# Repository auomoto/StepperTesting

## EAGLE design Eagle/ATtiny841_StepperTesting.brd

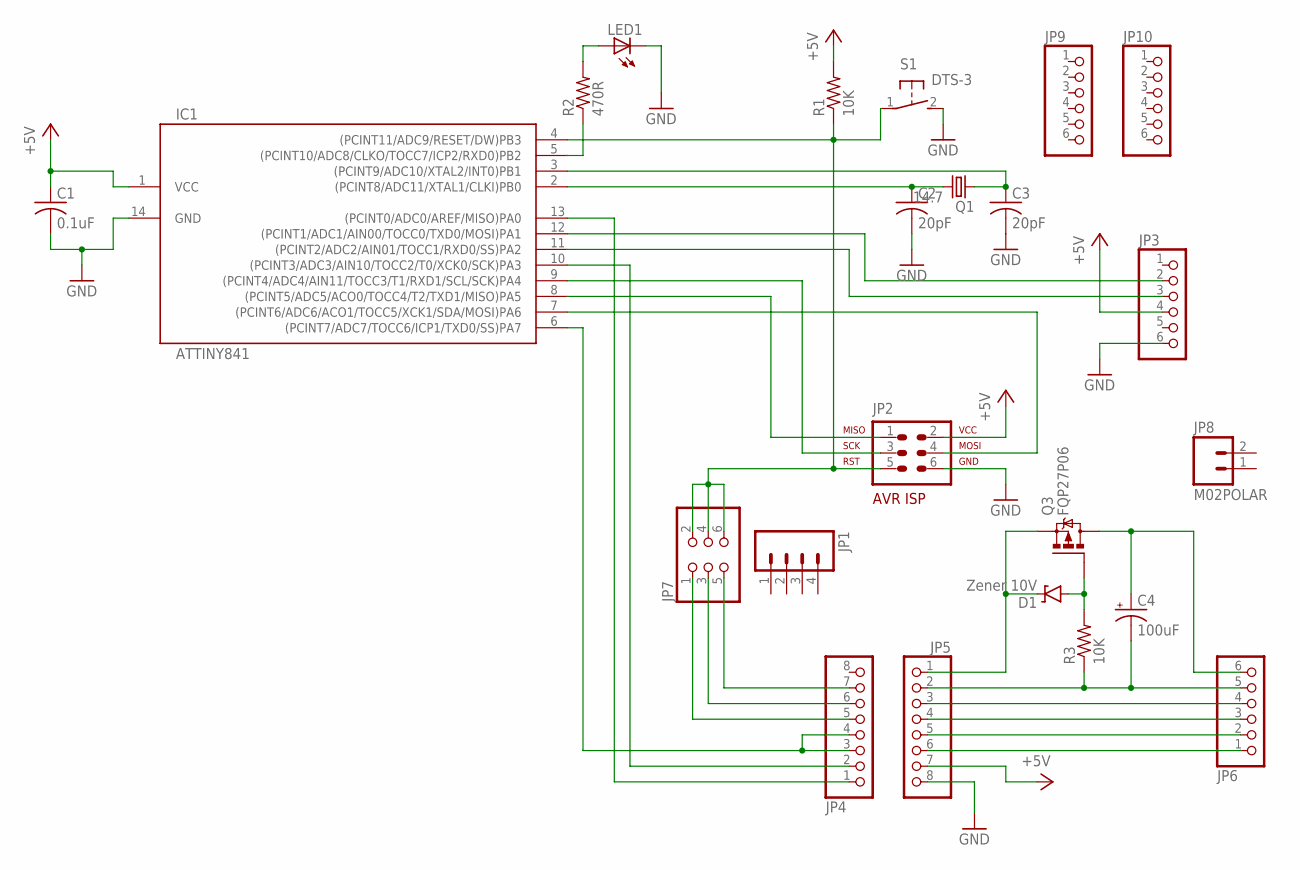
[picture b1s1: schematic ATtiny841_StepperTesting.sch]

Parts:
C1: 0.1uF; C025-024X044
C2, C3: 20pF; C025-024X044
C4: 100uF; E3,5-8
D1: Zener 10V; DIODE-ZENER
IC1: ATTINY841; SOIC14
JP1: M04POLAR; MOLEX-1X4
JP2: AVR-ISP-6VERT; AVR-ISP-6
JP3, JP6, JP9, JP10: PINHD-1X6CB; 1X06-CLEANBIG
JP4, JP5: PINHD-1X8CLEANBIG; 1X08-CLEANBIG
JP7: PINHD-2X3; 2X03
JP8: M02POLAR; MOLEX-1X2
LED1: LED5MM
Q1: 14.7; HC49/S
Q3: FQP27P06; TO220BV
R1, R3: 10K; 0207/7
R2: 470R; 0207/7
S1: DTS-3

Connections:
+5V: C1.1, IC1.1 (VCC), JP2.2, JP3.4, JP5.7, R1.2
DIR: IC1.13 ((PCINT0/ADC0/AREF/MISO)PA0), JP4.1
GND: C1.2, C2.2, C3.2, IC1.14 (GND), JP2.6, JP3.6, JP5.8, LED1.K (C), S1.2
MISO: IC1.8 ((PCINT5/ADC5/ACO0/TOCC4/T2/TXD1/MISO)PA5), JP2.1
MM-IN: C4.+, JP6.6, Q3.D
MOSI: IC1.7 ((PCINT6/ADC6/ACO1/TOCC5/XCK1/SDA/MOSI)P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), JP2.4
MOT-RET: C4.-, JP5.2, JP6.5, R3.1
MS1: JP4.7, JP7.5
MS2: JP4.6, JP7.3
MS3: JP4.5, JP7.1
unnamed: JP5.3, JP6.4
unnamed: LED1.A, R2.2
unnamed: JP5.4, JP6.3
unnamed: JP5.5, JP6.2
unnamed: JP5.6, JP6.1
unnamed: D1.P$2 (A), Q3.G, R3.2
PB2: IC1.5 ((PCINT10/ADC8/CLKO/TOCC7/ICP2/RXD0)PB2), R2.1
RST: IC1.4 ((PCINT11/ADC9/RESET/DW)PB3), JP2.5, JP7.2, JP7.4, JP7.6, R1.1, S1.1
RXD0: IC1.11 ((PCINT2/ADC2/AIN01/TOCC1/RXD0/SS)PA2), JP3.3
SCK: IC1.9 ((PCINT4/ADC4/AIN11/TOCC3/T1/RXD1/SCL/SC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), JP2.3
SLEEP: IC1.6 ((PCINT7/ADC7/TOCC6/ICP1/TXD0/SS)PA7), JP4.3, JP4.4
STEP: IC1.10 ((PCINT3/ADC3/AIN10/TOCC2/T0/XCK0/SCK)PA3), JP4.2
TXD0: IC1.12 ((PCINT1/ADC1/AIN00/TOCC0/TXD0/MOSI)PA1), JP3.2
VMOT: D1.P$1 (C), JP5.1, Q3.S
XTAL1: C3.1, IC1.3 ((PCINT9/ADC10/XTAL2/INT0)PB1), Q1.1
XTAL2: C2.1, IC1.2 ((PCINT8/ADC11/XTAL1/CLKI)PB0), Q1.2

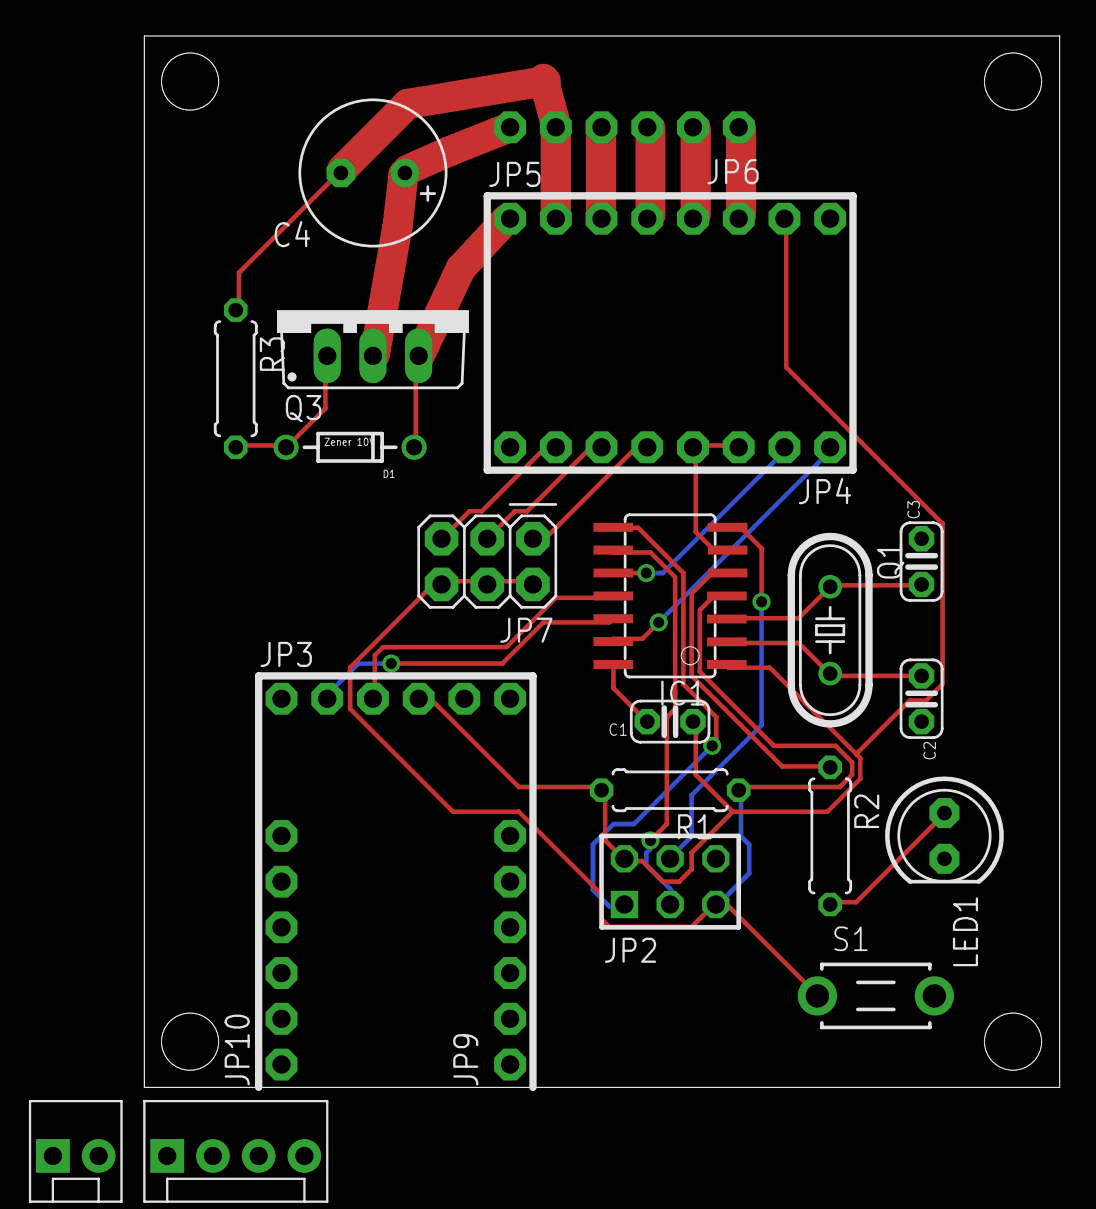
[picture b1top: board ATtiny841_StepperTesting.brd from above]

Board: 2 copper layers, 50.9 x 58.4 mm, 23 parts (0 on the bottom side), 26 nets.

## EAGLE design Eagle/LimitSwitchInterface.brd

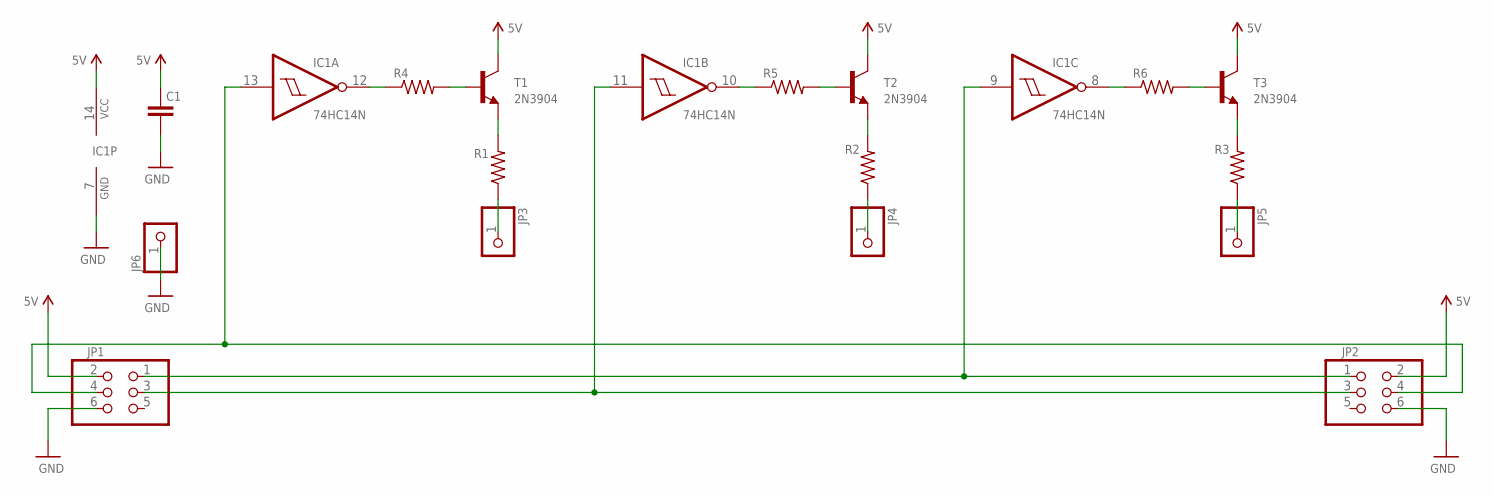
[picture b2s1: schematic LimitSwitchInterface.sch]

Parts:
C1: C-UNPOL; CAP-PTH-SMALL2
IC1: 74HC14N; DIL14
JP1, JP2: PINHD-2X3; 2X03
JP3, JP4, JP5, JP6: PINHD-1X1CB; 1X01-CLEANBIG
R1, R2, R3, R4, R5, R6: RESISTOR-0207/V; RESISTOR-0207/2V
T1, T2, T3: 2N3904

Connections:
5V: C1.1, IC1.14 (VCC), JP1.2, JP2.2, T1.3 (C), T2.3 (C), T3.3 (C)
GND: C1.2, IC1.7 (GND), JP1.6, JP2.6, JP6.1
unnamed: IC1.11 (I), JP1.3, JP2.3
unnamed: IC1.9 (I), JP1.1, JP2.1
unnamed: IC1.12 (O), R4.1
unnamed: IC1.13 (I), JP1.4, JP2.4
unnamed: IC1.10 (O), R5.1
unnamed: IC1.8 (O), R6.1
unnamed: JP3.1, R1.1
unnamed: JP4.1, R2.1
unnamed: JP5.1, R3.1
unnamed: R4.2, T1.2 (B)
unnamed: R5.2, T2.2 (B)
unnamed: R2.2, T2.1 (E)
unnamed: R6.2, T3.2 (B)
unnamed: R3.2, T3.1 (E)
unnamed: R1.2, T1.1 (E)

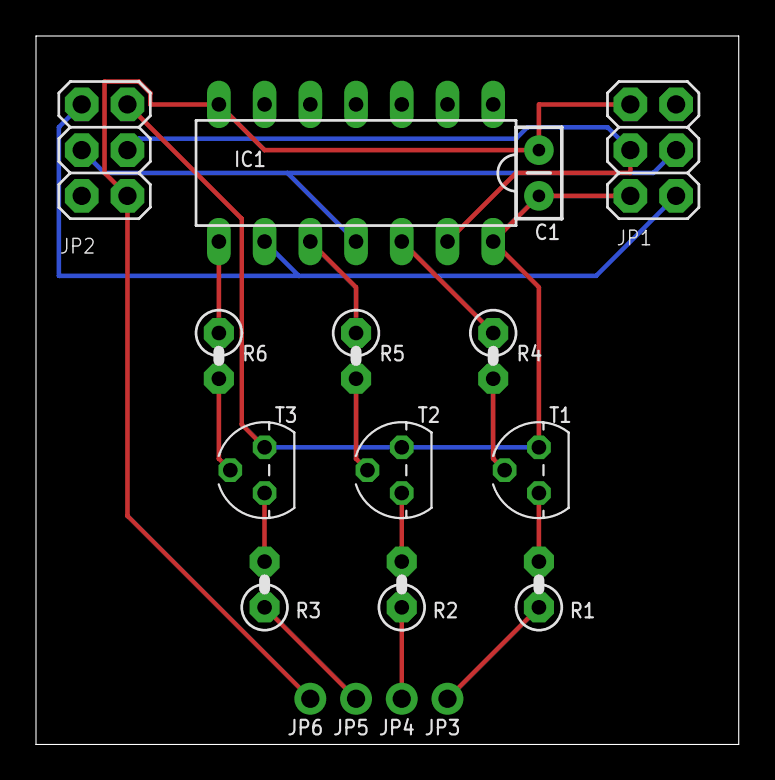
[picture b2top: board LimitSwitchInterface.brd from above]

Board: 2 copper layers, 39.0 x 39.4 mm, 17 parts (0 on the bottom side), 17 nets.

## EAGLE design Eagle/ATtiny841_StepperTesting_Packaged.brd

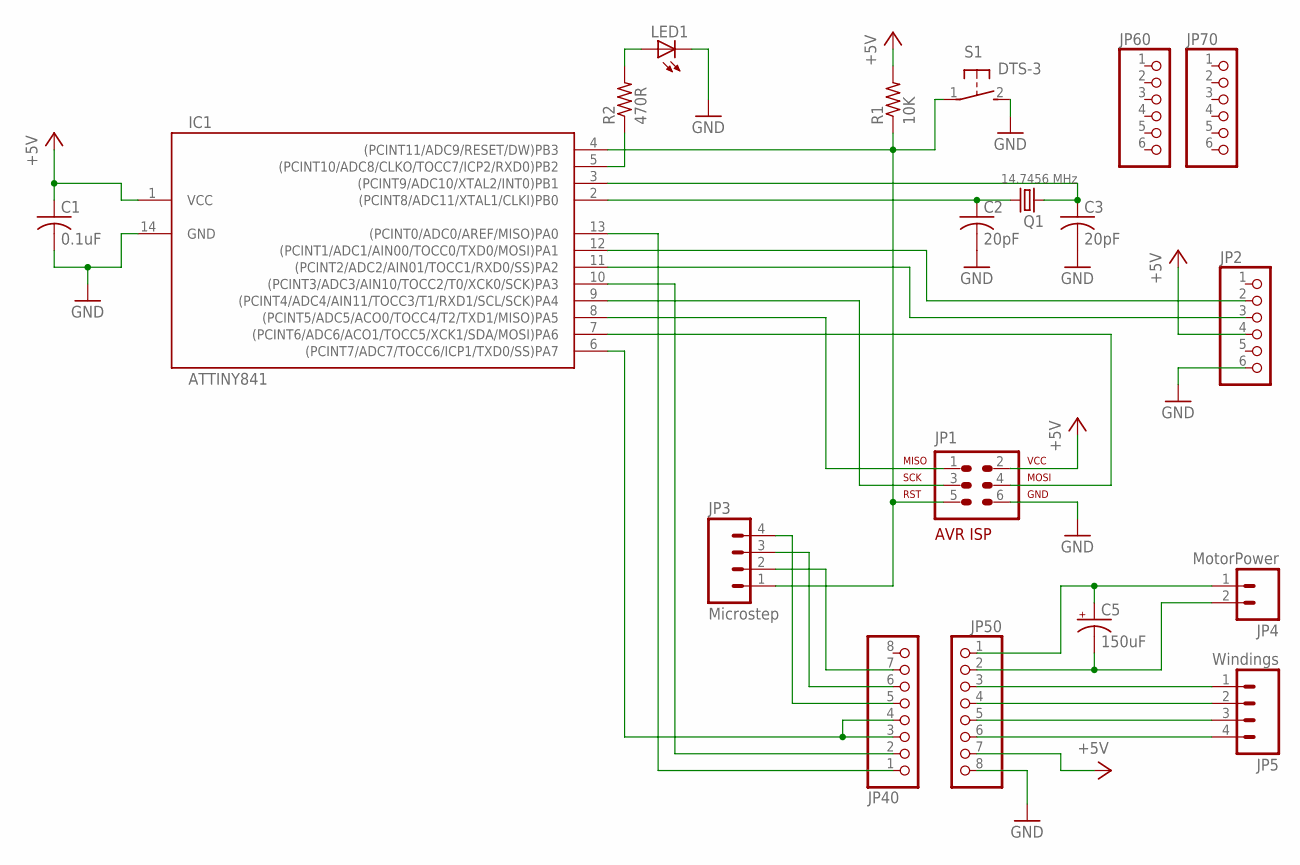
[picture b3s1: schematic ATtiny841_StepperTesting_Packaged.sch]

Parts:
C1: 0.1uF; C025-024X044
C2, C3: 20pF; C025-024X044
C5: 150uF; E7,5-18
IC1: ATTINY841; SOIC14
JP1: AVR-ISP-6VERT; AVR-ISP-6
JP2, JP60, JP70: PINHD-1X6CB; 1X06-CLEANBIG
JP3: Microstep; MOLEX-1X4
JP4: MotorPower; MOLEX-1X2
JP5: Windings; MOLEX-1X4
JP40, JP50: PINHD-1X8CLEANBIG; 1X08-CLEANBIG
LED1: LED5MM
Q1: 14.7456 MHz; HC49/S
R1: 10K; 0207/7
R2: 470R; 0207/7
S1: DTS-3

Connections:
+5V: C1.1, IC1.1 (VCC), JP1.2, JP2.4, JP50.7, R1.2
DIR: IC1.13 ((PCINT0/ADC0/AREF/MISO)PA0), JP40.1
GND: C1.2, C2.2, C3.2, IC1.14 (GND), JP1.6, JP2.6, JP50.8, LED1.K (C), S1.2
MISO: IC1.8 ((PCINT5/ADC5/ACO0/TOCC4/T2/TXD1/MISO)PA5), JP1.1
MOSI: IC1.7 ((PCINT6/ADC6/ACO1/TOCC5/XCK1/SDA/MOSI)P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), JP1.4
MOT-RET: C5.-, JP4.2, JP50.2
unnamed: JP3.4, JP40.5
unnamed: JP3.3, JP40.6
unnamed: JP3.2, JP40.7
unnamed: JP5.1, JP50.3
unnamed: LED1.A, R2.2
unnamed: JP5.2, JP50.4
unnamed: JP5.3, JP50.5
unnamed: JP5.4, JP50.6
PB2: IC1.5 ((PCINT10/ADC8/CLKO/TOCC7/ICP2/RXD0)PB2), R2.1
RST: IC1.4 ((PCINT11/ADC9/RESET/DW)PB3), JP1.5, JP3.1, R1.1, S1.1
RXD0: IC1.11 ((PCINT2/ADC2/AIN01/TOCC1/RXD0/SS)PA2), JP2.3
SCK: IC1.9 ((PCINT4/ADC4/AIN11/TOCC3/T1/RXD1/SCL/SC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), JP1.3
SLEEP: IC1.6 ((PCINT7/ADC7/TOCC6/ICP1/TXD0/SS)PA7), JP40.3, JP40.4
STEP: IC1.10 ((PCINT3/ADC3/AIN10/TOCC2/T0/XCK0/SCK)PA3), JP40.2
TXD0: IC1.12 ((PCINT1/ADC1/AIN00/TOCC0/TXD0/MOSI)PA1), JP2.2
VMOT: C5.+, JP4.1, JP50.1
XTAL1: C3.1, IC1.3 ((PCINT9/ADC10/XTAL2/INT0)PB1), Q1.1
XTAL2: C2.1, IC1.2 ((PCINT8/ADC11/XTAL1/CLKI)PB0), Q1.2

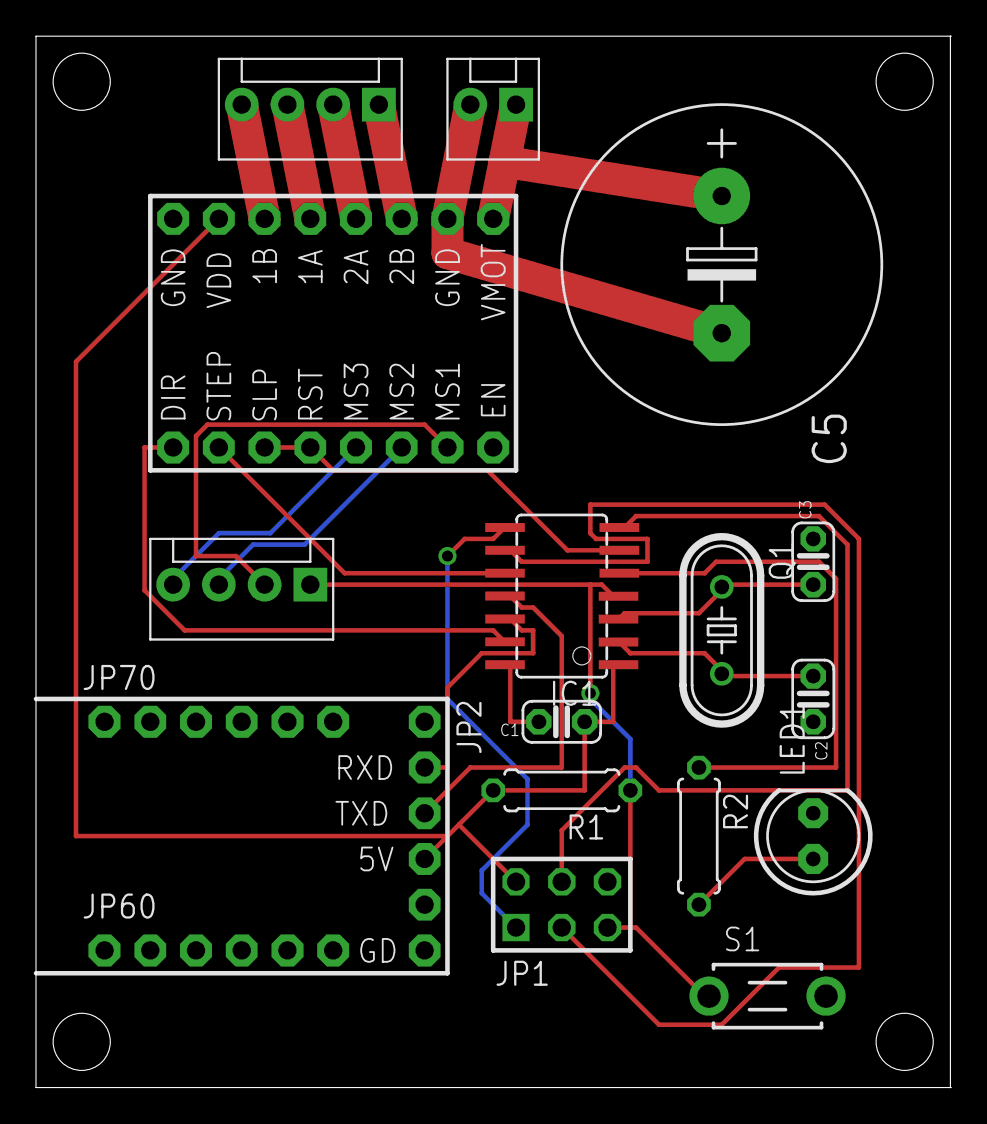
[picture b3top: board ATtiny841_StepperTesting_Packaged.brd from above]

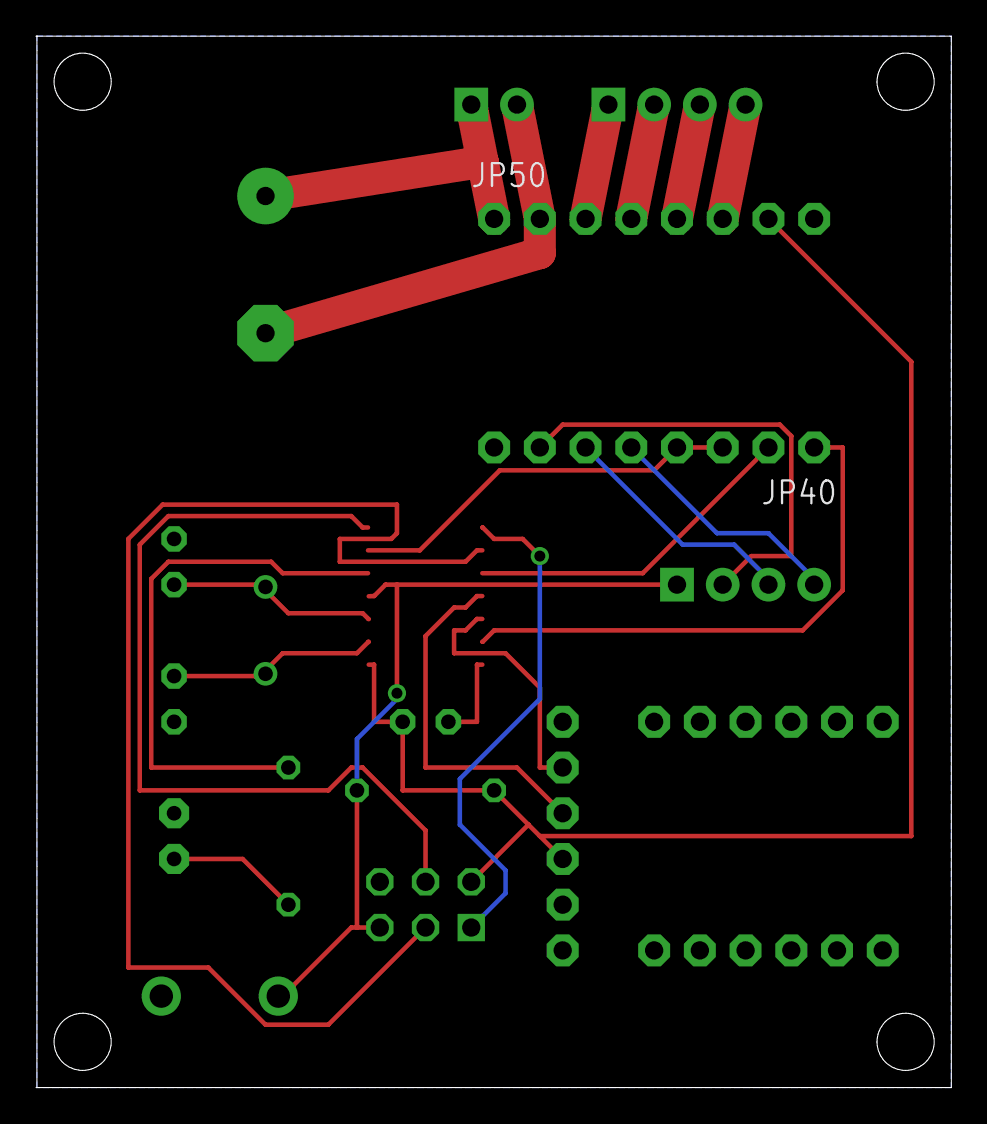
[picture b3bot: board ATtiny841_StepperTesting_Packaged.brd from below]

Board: 2 copper layers, 50.9 x 58.4 mm, 19 parts (2 on the bottom side), 24 nets.

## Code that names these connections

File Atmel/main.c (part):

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	an FTDI serial I/O connection (J1).

PIN CONFLICTS
	PA4 is SCK on the ISP
	PA5 is MISO on the ISP
	PA6 is MOSI on the ISP
	PB2 has an LED
	PB3 is the RESET pin

 */ 

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
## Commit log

2016-01-04 :neckbeard: Added .gitattributes & .gitignore files
2016-01-04 Initial commit main.c
    Command line program for stepper motor testing box.
2016-01-04 Initial commit for packaged schematic
    This one fits into the case I bought.
2016-01-04 nitial Commit
    Initial commit

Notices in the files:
parts and their libraries:
SparkFun-Connectors: Licensing: Creative Commons ShareAlike 4.0 International - https://creativecommons.org/licenses/by-sa/4.0
